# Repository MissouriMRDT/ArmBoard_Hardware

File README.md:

# RoboticArm-Hardware
Hardware design files for robotic arm

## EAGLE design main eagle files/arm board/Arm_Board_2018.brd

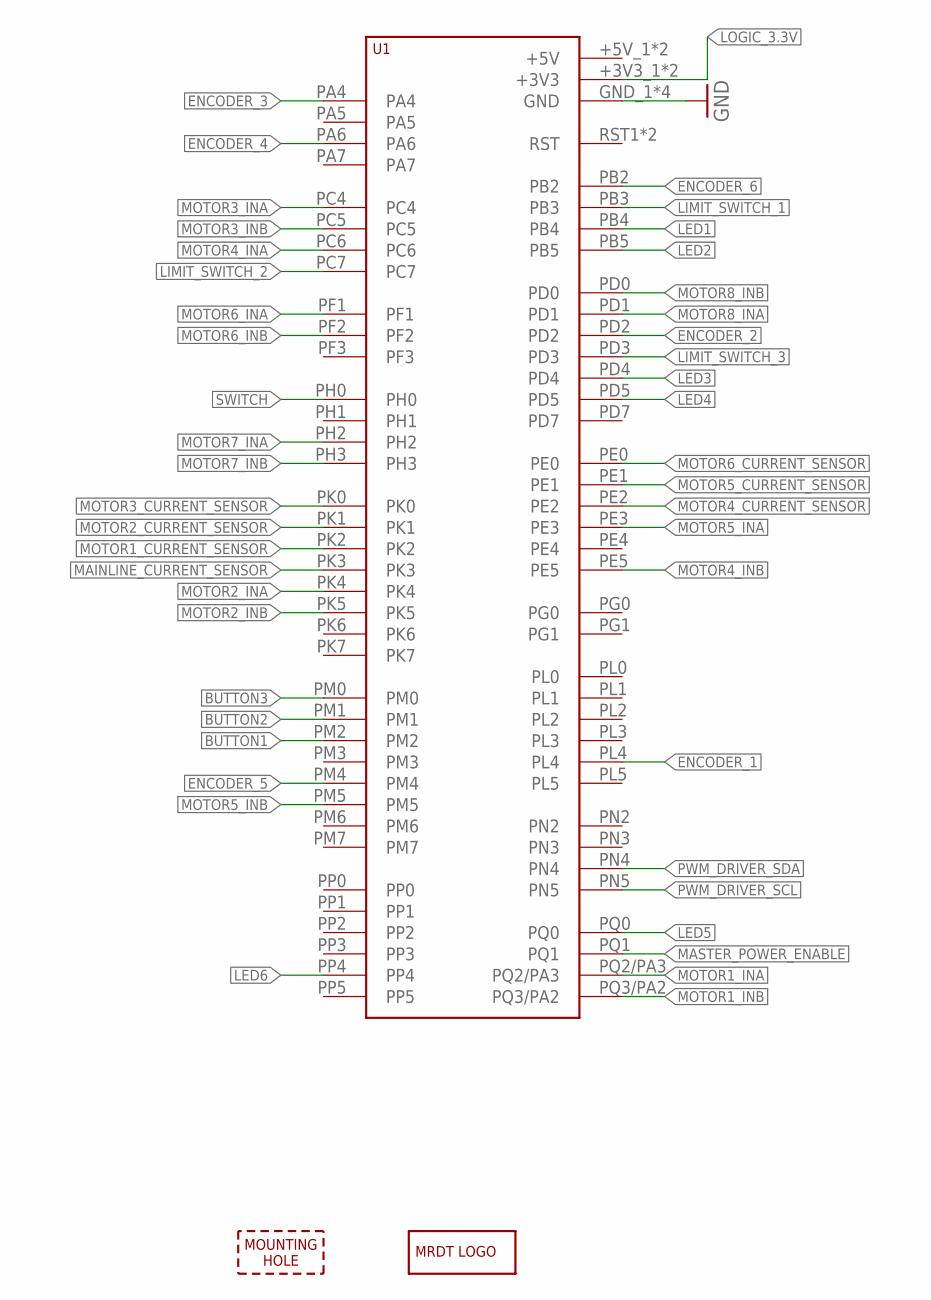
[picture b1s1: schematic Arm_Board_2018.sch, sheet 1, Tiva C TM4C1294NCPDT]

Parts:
H1: MOUNTING_HOLE#6; #6_SCREW
LOGO1: MRDT_LOGO
U1: TIVA-1294; TIVA-C-CONNECTED

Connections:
BUTTON1: U1.PM2; also elsewhere on the board
BUTTON2: U1.PM1; also elsewhere on the board
BUTTON3: U1.PM0; also elsewhere on the board
ENCODER_1: U1.PL4; also elsewhere on the board
ENCODER_2: U1.PD2; also elsewhere on the board
ENCODER_3: U1.PA4; also elsewhere on the board
ENCODER_4: U1.PA6; also elsewhere on the board
ENCODER_5: U1.PM4; also elsewhere on the board
ENCODER_6: U1.PB2; also elsewhere on the board
GND: U1.GND_1 (GND), U1.GND_2 (GND), U1.GND_3 (GND), U1.GND_4 (GND); also elsewhere on the board
LED1: U1.PB4; also elsewhere on the board
LED2: U1.PB5; also elsewhere on the board
LED3: U1.PD4; also elsewhere on the board
LED4: U1.PD5; also elsewhere on the board
LED5: U1.PQ0; also elsewhere on the board
LED6: U1.PP4; also elsewhere on the board
LIMIT_SWITCH_1: U1.PB3; also elsewhere on the board
LIMIT_SWITCH_2: U1.PC7; also elsewhere on the board
LIMIT_SWITCH_3: U1.PD3; also elsewhere on the board
LOGIC_3.3V: U1.+3V3_1 (+3V3), U1.+3V3_2 (+3V3); also elsewhere on the board
MAINLINE_CURRENT_SENSOR: U1.PK3; also elsewhere on the board
MASTER_POWER_ENABLE: U1.PQ1; also elsewhere on the board
MOTOR1_CURRENT_SENSOR: U1.PK2; also elsewhere on the board
MOTOR1_INA: U1.PQ2/PA3; also elsewhere on the board
MOTOR1_INB: U1.PQ3/PA2; also elsewhere on the board
MOTOR2_CURRENT_SENSOR: U1.PK1; also elsewhere on the board
MOTOR2_INA: U1.PK4; also elsewhere on the board
MOTOR2_INB: U1.PK5; also elsewhere on the board
MOTOR3_CURRENT_SENSOR: U1.PK0; also elsewhere on the board
MOTOR3_INA: U1.PC4; also elsewhere on the board
MOTOR3_INB: U1.PC5; also elsewhere on the board
MOTOR4_CURRENT_SENSOR: U1.PE2; also elsewhere on the board
MOTOR4_INA: U1.PC6; also elsewhere on the board
MOTOR4_INB: U1.PE5; also elsewhere on the board
MOTOR5_CURRENT_SENSOR: U1.PE1; also elsewhere on the board
MOTOR5_INA: U1.PE3; also elsewhere on the board
MOTOR5_INB: U1.PM5; also elsewhere on the board
MOTOR6_CURRENT_SENSOR: U1.PE0; also elsewhere on the board
MOTOR6_INA: U1.PF1; also elsewhere on the board
MOTOR6_INB: U1.PF2; also elsewhere on the board
MOTOR7_INA: U1.PH2; also elsewhere on the board
MOTOR7_INB: U1.PH3; also elsewhere on the board
MOTOR8_INA: U1.PD1; also elsewhere on the board
MOTOR8_INB: U1.PD0; also elsewhere on the board
PWM_DRIVER_SCL: U1.PN5; also elsewhere on the board
PWM_DRIVER_SDA: U1.PN4; also elsewhere on the board
SWITCH: U1.PH0; also elsewhere on the board

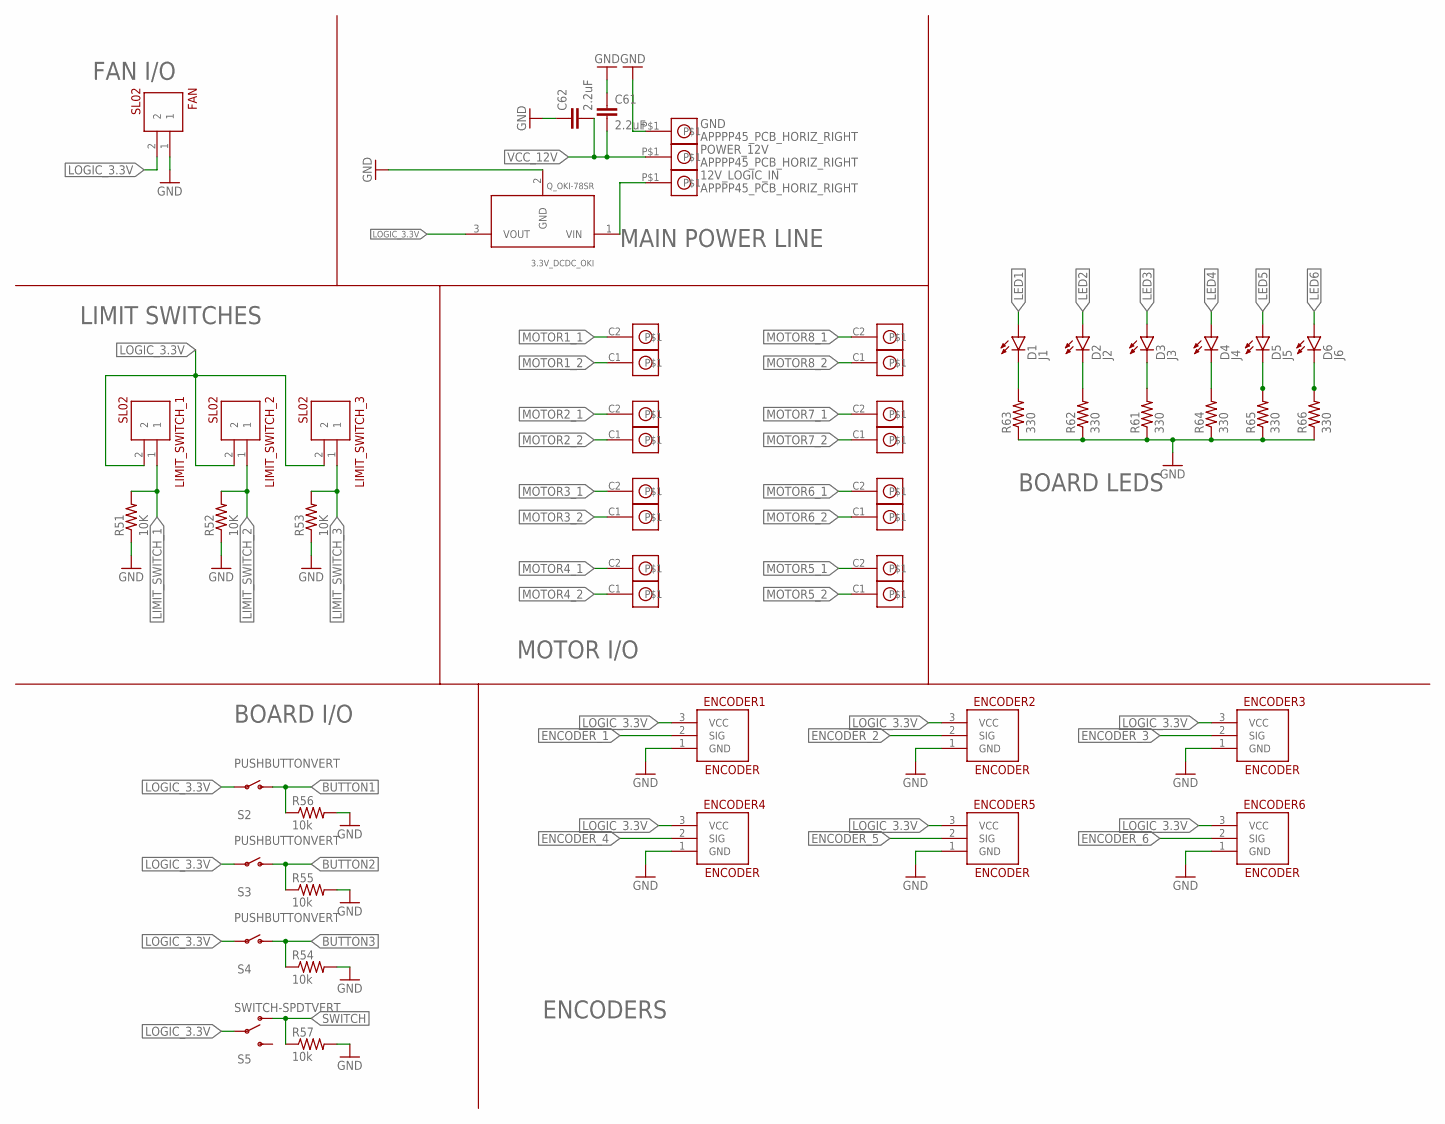
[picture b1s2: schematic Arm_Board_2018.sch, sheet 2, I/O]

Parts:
3.3V_DCDC_OKI: Q_OKI-78SR
12V_LOGIC_IN: APPPP45_PCB_HORIZ_RIGHT; APP45_PCB_HORIZ_RIGHT
C61, C62: 2.2uF; 1206
D1: J1; LED-0603
D2: J2; LED-0603
D3: J3; LED-0603
D4: J4; LED-0603
D5: J5; LED-0603
D6: J6; LED-0603
ENCODER1, ENCODER2, ENCODER3, ENCODER4, ENCODER5, ENCODER6: ENCODER; MOLEX-70543-0002
FAN: SL02; MOLEX-70543-0001
GND: APPPP45_PCB_HORIZ_RIGHT; APP45_PCB_HORIZ_RIGHT
LIMIT_SWITCH_1, LIMIT_SWITCH_2, LIMIT_SWITCH_3: SL02; MOLEX-70543-0001
MOTOR1, MOTOR2, MOTOR3, MOTOR4, MOTOR5, MOTOR6, MOTOR7, MOTOR8: APP_2POS_CONFIGGENERAL_CONFIG; APP45_HORIZ_CONFIG
POWER_12V: APPPP45_PCB_HORIZ_RIGHT; APP45_PCB_HORIZ_RIGHT
R51, R52, R53: 10K; 0402-RES
R54, R55, R56, R57: 10k; 0402-RES
R61, R62, R63, R64, R65, R66: 330; 0402-RES
S2, S3, S4: PUSHBUTTONVERT; APEM-MJTP1243
S5: SWITCH-SPDTVERT; C&K-SS12D07VG4NSGAPA

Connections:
BUTTON1: R56.1, S2.P$2 (S); also elsewhere on the board
BUTTON2: R55.1, S3.P$2 (S); also elsewhere on the board
BUTTON3: R54.1, S4.P$2 (S); also elsewhere on the board
ENCODER_1: ENCODER1.2 (SIG); also elsewhere on the board
ENCODER_2: ENCODER2.2 (SIG); also elsewhere on the board
ENCODER_3: ENCODER3.2 (SIG); also elsewhere on the board
ENCODER_4: ENCODER4.2 (SIG); also elsewhere on the board
ENCODER_5: ENCODER5.2 (SIG); also elsewhere on the board
ENCODER_6: ENCODER6.2 (SIG); also elsewhere on the board
GND: 3.3V_DCDC_OKI.2 (GND), C61.1, C62.1, ENCODER1.1 (GND), ENCODER2.1 (GND), ENCODER3.1 (GND), ENCODER4.1 (GND), ENCODER5.1 (GND), ENCODER6.1 (GND), FAN.1, GND.P$1, R51.1, R52.1, R53.1, R54.2, R55.2, R56.2, R57.2, R61.1, R62.1, R63.1, R64.1, R65.1, R66.1; also elsewhere on the board
LED1: D1.A; also elsewhere on the board
LED2: D2.A; also elsewhere on the board
LED3: D3.A; also elsewhere on the board
LED4: D4.A; also elsewhere on the board
LED5: D5.A; also elsewhere on the board
LED6: D6.A; also elsewhere on the board
LIMIT_SWITCH_1: LIMIT_SWITCH_1.1, R51.2; also elsewhere on the board
LIMIT_SWITCH_2: LIMIT_SWITCH_2.1, R52.2; also elsewhere on the board
LIMIT_SWITCH_3: LIMIT_SWITCH_3.1, R53.2; also elsewhere on the board
LOGIC_3.3V: 3.3V_DCDC_OKI.3 (VOUT), ENCODER1.3 (VCC), ENCODER2.3 (VCC), ENCODER3.3 (VCC), ENCODER4.3 (VCC), ENCODER5.3 (VCC), ENCODER6.3 (VCC), FAN.2, LIMIT_SWITCH_1.2, LIMIT_SWITCH_2.2, LIMIT_SWITCH_3.2, S2.P$1, S3.P$1, S4.P$1, S5.P$2; also elsewhere on the board
MOTOR1_1: MOTOR1.C2; also elsewhere on the board
MOTOR1_2: MOTOR1.C1; also elsewhere on the board
MOTOR2_1: MOTOR2.C2; also elsewhere on the board
MOTOR2_2: MOTOR2.C1; also elsewhere on the board
MOTOR3_1: MOTOR3.C2; also elsewhere on the board
MOTOR3_2: MOTOR3.C1; also elsewhere on the board
MOTOR4_1: MOTOR4.C2; also elsewhere on the board
MOTOR4_2: MOTOR4.C1; also elsewhere on the board
MOTOR5_1: MOTOR5.C2; also elsewhere on the board
MOTOR5_2: MOTOR5.C1; also elsewhere on the board
MOTOR6_1: MOTOR6.C2; also elsewhere on the board
MOTOR6_2: MOTOR6.C1; also elsewhere on the board
MOTOR7_1: MOTOR7.C2; also elsewhere on the board
MOTOR7_2: MOTOR7.C1; also elsewhere on the board
MOTOR8_1: MOTOR8.C2; also elsewhere on the board
MOTOR8_2: MOTOR8.C1; also elsewhere on the board
unnamed: 3.3V_DCDC_OKI.1 (VIN), 12V_LOGIC_IN.P$1
unnamed: D1.C, R63.2
unnamed: D2.C, R62.2
unnamed: D6.C, R66.2
unnamed: D3.C, R61.2
unnamed: D4.C, R64.2
unnamed: D5.C, R65.2
SWITCH: R57.1, S5.P$3 (O); also elsewhere on the board
VCC_12V: C61.2, C62.2, POWER_12V.P$1; also elsewhere on the board

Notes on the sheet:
FAN I/O
MOTOR I/O
MAIN POWER LINE
LIMIT SWITCHES
ENCODERS
BOARD I/O
BOARD LEDS

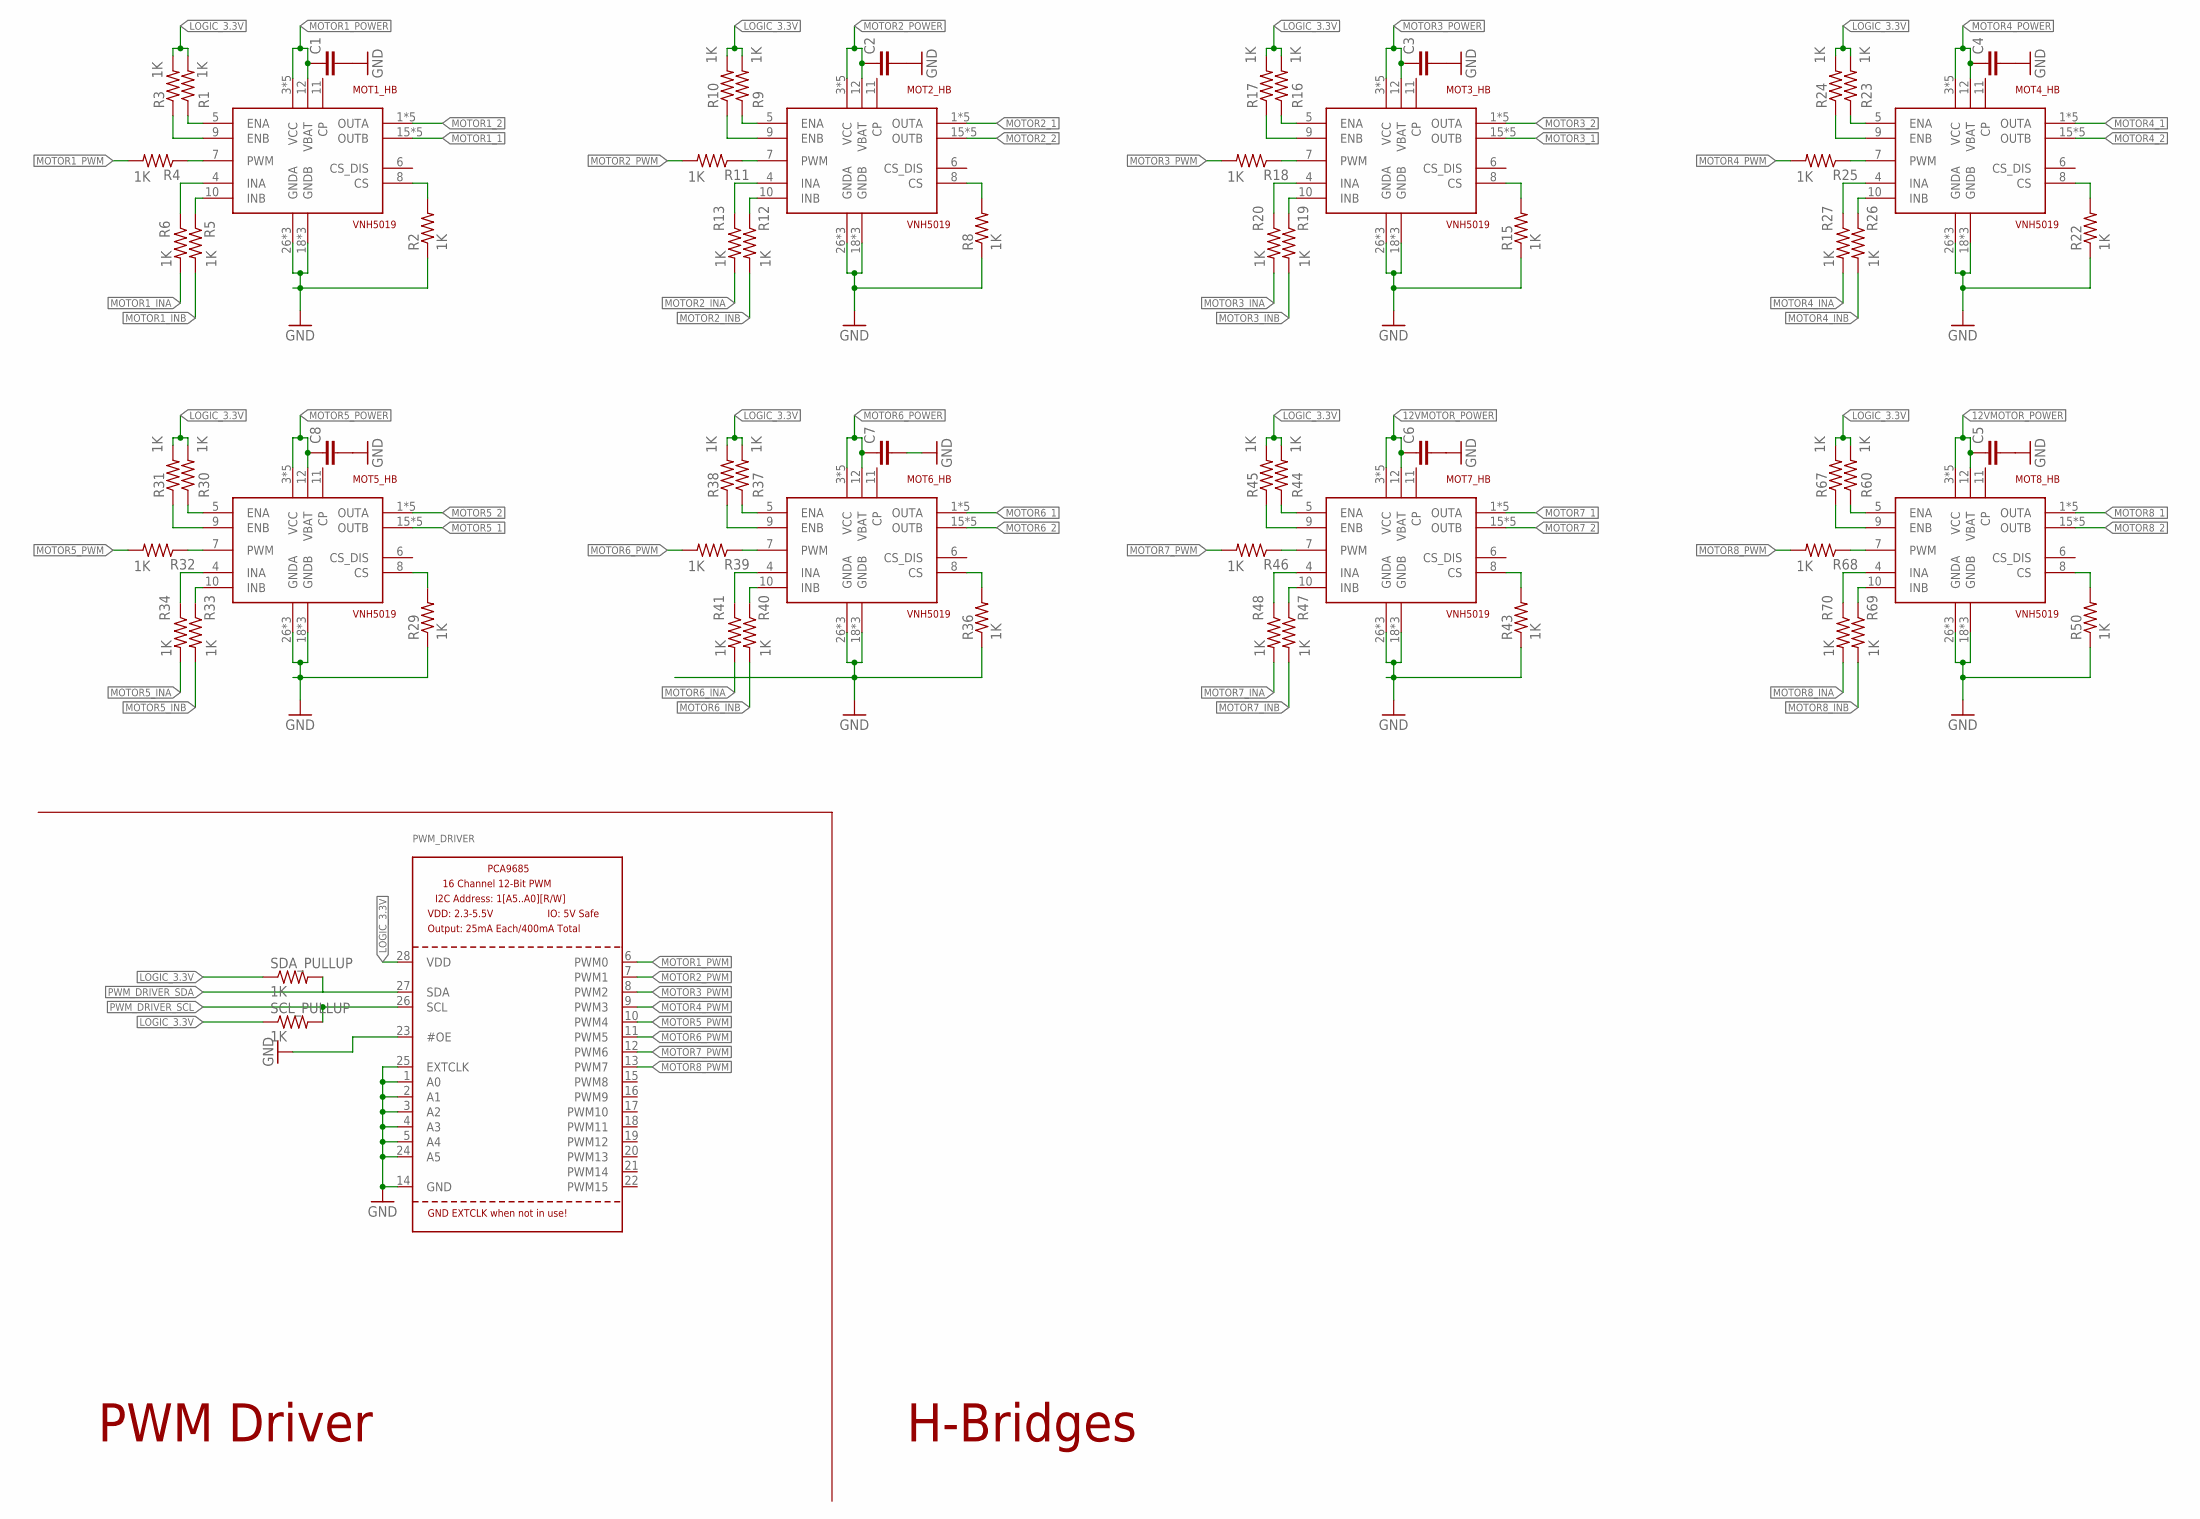
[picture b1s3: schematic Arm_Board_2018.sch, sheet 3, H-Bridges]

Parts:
C1, C2, C3, C4, C5, C6, C7, C8: CAP1210; 1210
MOT1_HB, MOT2_HB, MOT3_HB, MOT4_HB, MOT5_HB, MOT6_HB, MOT7_HB, MOT8_HB: VNH5019; MULTIPOWERSO-30
PWM_DRIVER: PCA9685; TSSOP28
R1, R2, R3, R4, R5, R6, R8, R9, R10, R11, R12, R13, R15, R16, R17, R18, R19, R20, R22, R23, R24, R25, R26, R27, R29, R30, R31, R32, R33, R34, R36, R37, R38, R39, R40, R41, R43, R44, R45, R46, R47, R48, R50, R60, R67, R68, R69, R70: 1K; 0603-RES
SCL_PULLUP: 1K; 0402-RES
SDA_PULLUP: 1K; 0402-RES

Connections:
12VMOTOR_POWER: C5.1, C6.1, MOT7_HB.3 (VCC), MOT7_HB.12 (VBAT), MOT7_HB.13 (VCC), MOT7_HB.23 (VCC), MOT7_HB.VCC, MOT7_HB.VCC@1 (VCC), MOT8_HB.3 (VCC), MOT8_HB.12 (VBAT), MOT8_HB.13 (VCC), MOT8_HB.23 (VCC), MOT8_HB.VCC, MOT8_HB.VCC@1 (VCC); also elsewhere on the board
GND: C1.2, C2.2, C3.2, C4.2, C5.2, C6.2, C7.2, C8.2, MOT1_HB.18 (GNDB), MOT1_HB.19 (GNDB), MOT1_HB.20 (GNDB), MOT1_HB.26 (GNDA), MOT1_HB.27 (GNDA), MOT1_HB.28 (GNDA), MOT2_HB.18 (GNDB), MOT2_HB.19 (GNDB), MOT2_HB.20 (GNDB), MOT2_HB.26 (GNDA), MOT2_HB.27 (GNDA), MOT2_HB.28 (GNDA), MOT3_HB.18 (GNDB), MOT3_HB.19 (GNDB), MOT3_HB.20 (GNDB), MOT3_HB.26 (GNDA), MOT3_HB.27 (GNDA), MOT3_HB.28 (GNDA), MOT4_HB.18 (GNDB), MOT4_HB.19 (GNDB), MOT4_HB.20 (GNDB), MOT4_HB.26 (GNDA), MOT4_HB.27 (GNDA), MOT4_HB.28 (GNDA), MOT5_HB.18 (GNDB), MOT5_HB.19 (GNDB), MOT5_HB.20 (GNDB), MOT5_HB.26 (GNDA), MOT5_HB.27 (GNDA), MOT5_HB.28 (GNDA), MOT6_HB.18 (GNDB), MOT6_HB.19 (GNDB), MOT6_HB.20 (GNDB), MOT6_HB.26 (GNDA), MOT6_HB.27 (GNDA), MOT6_HB.28 (GNDA), MOT7_HB.18 (GNDB), MOT7_HB.19 (GNDB), MOT7_HB.20 (GNDB), MOT7_HB.26 (GNDA), MOT7_HB.27 (GNDA), MOT7_HB.28 (GNDA), MOT8_HB.18 (GNDB), MOT8_HB.19 (GNDB), MOT8_HB.20 (GNDB), MOT8_HB.26 (GNDA), MOT8_HB.27 (GNDA), MOT8_HB.28 (GNDA), PWM_DRIVER.1 (A0), PWM_DRIVER.2 (A1), PWM_DRIVER.3 (A2), PWM_DRIVER.4 (A3), PWM_DRIVER.5 (A4), PWM_DRIVER.14 (GND), PWM_DRIVER.23 (#OE), PWM_DRIVER.24 (A5), PWM_DRIVER.25 (EXTCLK), R2.1, R8.1, R15.1, R22.1, R29.1, R36.1, R43.1, R50.1; also elsewhere on the board
LOGIC_3.3V: PWM_DRIVER.28 (VDD), R1.2, R3.2, R9.2, R10.2, R16.2, R17.2, R23.2, R24.2, R30.2, R31.2, R37.2, R38.2, R44.2, R45.2, R60.2, R67.2, SCL_PULLUP.1, SDA_PULLUP.1; also elsewhere on the board
MOTOR1_1: MOT1_HB.15 (OUTB), MOT1_HB.16 (OUTB), MOT1_HB.21 (OUTB), MOT1_HB.OUTB, MOT1_HB.OUTB@1 (OUTB); also elsewhere on the board
MOTOR1_2: MOT1_HB.1 (OUTA), MOT1_HB.25 (OUTA), MOT1_HB.30 (OUTA), MOT1_HB.OUTA, MOT1_HB.OUTA@1 (OUTA); also elsewhere on the board
MOTOR1_INA: R6.2; also elsewhere on the board
MOTOR1_INB: R5.2; also elsewhere on the board
MOTOR1_POWER: C1.1, MOT1_HB.3 (VCC), MOT1_HB.12 (VBAT), MOT1_HB.13 (VCC), MOT1_HB.23 (VCC), MOT1_HB.VCC, MOT1_HB.VCC@1 (VCC); also elsewhere on the board
MOTOR1_PWM: PWM_DRIVER.6 (PWM0), R4.2
MOTOR2_1: MOT2_HB.1 (OUTA), MOT2_HB.25 (OUTA), MOT2_HB.30 (OUTA), MOT2_HB.OUTA, MOT2_HB.OUTA@1 (OUTA); also elsewhere on the board
MOTOR2_2: MOT2_HB.15 (OUTB), MOT2_HB.16 (OUTB), MOT2_HB.21 (OUTB), MOT2_HB.OUTB, MOT2_HB.OUTB@1 (OUTB); also elsewhere on the board
MOTOR2_INA: R13.2; also elsewhere on the board
MOTOR2_INB: R12.2; also elsewhere on the board
MOTOR2_POWER: C2.1, MOT2_HB.3 (VCC), MOT2_HB.12 (VBAT), MOT2_HB.13 (VCC), MOT2_HB.23 (VCC), MOT2_HB.VCC, MOT2_HB.VCC@1 (VCC); also elsewhere on the board
MOTOR2_PWM: PWM_DRIVER.7 (PWM1), R11.2
MOTOR3_1: MOT3_HB.15 (OUTB), MOT3_HB.16 (OUTB), MOT3_HB.21 (OUTB), MOT3_HB.OUTB, MOT3_HB.OUTB@1 (OUTB); also elsewhere on the board
MOTOR3_2: MOT3_HB.1 (OUTA), MOT3_HB.25 (OUTA), MOT3_HB.30 (OUTA), MOT3_HB.OUTA, MOT3_HB.OUTA@1 (OUTA); also elsewhere on the board
MOTOR3_INA: R20.2; also elsewhere on the board
MOTOR3_INB: R19.2; also elsewhere on the board
MOTOR3_POWER: C3.1, MOT3_HB.3 (VCC), MOT3_HB.12 (VBAT), MOT3_HB.13 (VCC), MOT3_HB.23 (VCC), MOT3_HB.VCC, MOT3_HB.VCC@1 (VCC); also elsewhere on the board
MOTOR3_PWM: PWM_DRIVER.8 (PWM2), R18.2
MOTOR4_1: MOT4_HB.1 (OUTA), MOT4_HB.25 (OUTA), MOT4_HB.30 (OUTA), MOT4_HB.OUTA, MOT4_HB.OUTA@1 (OUTA); also elsewhere on the board
MOTOR4_2: MOT4_HB.15 (OUTB), MOT4_HB.16 (OUTB), MOT4_HB.21 (OUTB), MOT4_HB.OUTB, MOT4_HB.OUTB@1 (OUTB); also elsewhere on the board
MOTOR4_INA: R27.2; also elsewhere on the board
MOTOR4_INB: R26.2; also elsewhere on the board
MOTOR4_POWER: C4.1, MOT4_HB.3 (VCC), MOT4_HB.12 (VBAT), MOT4_HB.13 (VCC), MOT4_HB.23 (VCC), MOT4_HB.VCC, MOT4_HB.VCC@1 (VCC); also elsewhere on the board
MOTOR4_PWM: PWM_DRIVER.9 (PWM3), R25.2
MOTOR5_1: MOT5_HB.15 (OUTB), MOT5_HB.16 (OUTB), MOT5_HB.21 (OUTB), MOT5_HB.OUTB, MOT5_HB.OUTB@1 (OUTB); also elsewhere on the board
MOTOR5_2: MOT5_HB.1 (OUTA), MOT5_HB.25 (OUTA), MOT5_HB.30 (OUTA), MOT5_HB.OUTA, MOT5_HB.OUTA@1 (OUTA); also elsewhere on the board
MOTOR5_INA: R34.2; also elsewhere on the board
MOTOR5_INB: R33.2; also elsewhere on the board
MOTOR5_POWER: C8.1, MOT5_HB.3 (VCC), MOT5_HB.12 (VBAT), MOT5_HB.13 (VCC), MOT5_HB.23 (VCC), MOT5_HB.VCC, MOT5_HB.VCC@1 (VCC); also elsewhere on the board
MOTOR5_PWM: PWM_DRIVER.10 (PWM4), R32.2
MOTOR6_1: MOT6_HB.1 (OUTA), MOT6_HB.25 (OUTA), MOT6_HB.30 (OUTA), MOT6_HB.OUTA, MOT6_HB.OUTA@1 (OUTA); also elsewhere on the board
MOTOR6_2: MOT6_HB.15 (OUTB), MOT6_HB.16 (OUTB), MOT6_HB.21 (OUTB), MOT6_HB.OUTB, MOT6_HB.OUTB@1 (OUTB); also elsewhere on the board
MOTOR6_INA: R41.2; also elsewhere on the board
MOTOR6_INB: R40.2; also elsewhere on the board
MOTOR6_POWER: C7.1, MOT6_HB.3 (VCC), MOT6_HB.12 (VBAT), MOT6_HB.13 (VCC), MOT6_HB.23 (VCC), MOT6_HB.VCC, MOT6_HB.VCC@1 (VCC); also elsewhere on the board
MOTOR6_PWM: PWM_DRIVER.11 (PWM5), R39.2
MOTOR7_1: MOT7_HB.1 (OUTA), MOT7_HB.25 (OUTA), MOT7_HB.30 (OUTA), MOT7_HB.OUTA, MOT7_HB.OUTA@1 (OUTA); also elsewhere on the board
MOTOR7_2: MOT7_HB.15 (OUTB), MOT7_HB.16 (OUTB), MOT7_HB.21 (OUTB), MOT7_HB.OUTB, MOT7_HB.OUTB@1 (OUTB); also elsewhere on the board
MOTOR7_INA: R48.2; also elsewhere on the board
MOTOR7_INB: R47.2; also elsewhere on the board
MOTOR7_PWM: PWM_DRIVER.12 (PWM6), R46.2
MOTOR8_1: MOT8_HB.1 (OUTA), MOT8_HB.25 (OUTA), MOT8_HB.30 (OUTA), MOT8_HB.OUTA, MOT8_HB.OUTA@1 (OUTA); also elsewhere on the board
MOTOR8_2: MOT8_HB.15 (OUTB), MOT8_HB.16 (OUTB), MOT8_HB.21 (OUTB), MOT8_HB.OUTB, MOT8_HB.OUTB@1 (OUTB); also elsewhere on the board
MOTOR8_INA: R70.2; also elsewhere on the board
MOTOR8_INB: R69.2; also elsewhere on the board
MOTOR8_PWM: PWM_DRIVER.13 (PWM7), R68.2
unnamed: MOT2_HB.8 (CS), R8.2
unnamed: MOT1_HB.8 (CS), R2.2
unnamed: MOT1_HB.5 (ENA), R1.1
unnamed: MOT1_HB.9 (ENB), R3.1
unnamed: MOT1_HB.7 (PWM), R4.1
unnamed: MOT1_HB.10 (INB), R5.1
unnamed: MOT1_HB.4 (INA), R6.1
unnamed: MOT2_HB.5 (ENA), R9.1
unnamed: MOT2_HB.9 (ENB), R10.1
unnamed: MOT2_HB.7 (PWM), R11.1
unnamed: MOT2_HB.10 (INB), R12.1
unnamed: MOT2_HB.4 (INA), R13.1
unnamed: MOT3_HB.8 (CS), R15.2
unnamed: MOT3_HB.5 (ENA), R16.1
unnamed: MOT3_HB.9 (ENB), R17.1
unnamed: MOT3_HB.7 (PWM), R18.1
unnamed: MOT3_HB.10 (INB), R19.1
unnamed: MOT3_HB.4 (INA), R20.1
unnamed: MOT4_HB.8 (CS), R22.2
unnamed: MOT4_HB.5 (ENA), R23.1
unnamed: MOT4_HB.9 (ENB), R24.1
unnamed: MOT4_HB.7 (PWM), R25.1
unnamed: MOT4_HB.10 (INB), R26.1
unnamed: MOT4_HB.4 (INA), R27.1
unnamed: MOT5_HB.8 (CS), R29.2
unnamed: MOT5_HB.5 (ENA), R30.1
unnamed: MOT5_HB.9 (ENB), R31.1
unnamed: MOT5_HB.7 (PWM), R32.1
unnamed: MOT5_HB.10 (INB), R33.1
unnamed: MOT5_HB.4 (INA), R34.1
unnamed: MOT6_HB.8 (CS), R36.2
unnamed: MOT6_HB.5 (ENA), R37.1
unnamed: MOT6_HB.9 (ENB), R38.1
unnamed: MOT6_HB.7 (PWM), R39.1
unnamed: MOT6_HB.10 (INB), R40.1
unnamed: MOT6_HB.4 (INA), R41.1
unnamed: MOT7_HB.8 (CS), R43.2
unnamed: MOT7_HB.5 (ENA), R44.1
unnamed: MOT7_HB.9 (ENB), R45.1
unnamed: MOT7_HB.7 (PWM), R46.1
unnamed: MOT7_HB.10 (INB), R47.1
unnamed: MOT7_HB.4 (INA), R48.1
unnamed: MOT8_HB.8 (CS), R50.2
unnamed: MOT8_HB.5 (ENA), R60.1
unnamed: MOT8_HB.9 (ENB), R67.1
unnamed: MOT8_HB.7 (PWM), R68.1
unnamed: MOT8_HB.10 (INB), R69.1
unnamed: MOT8_HB.4 (INA), R70.1
PWM_DRIVER_SCL: PWM_DRIVER.26 (SCL), SCL_PULLUP.2; also elsewhere on the board
PWM_DRIVER_SDA: PWM_DRIVER.27 (SDA), SDA_PULLUP.2; also elsewhere on the board

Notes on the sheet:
PWM Driver
H-Bridges

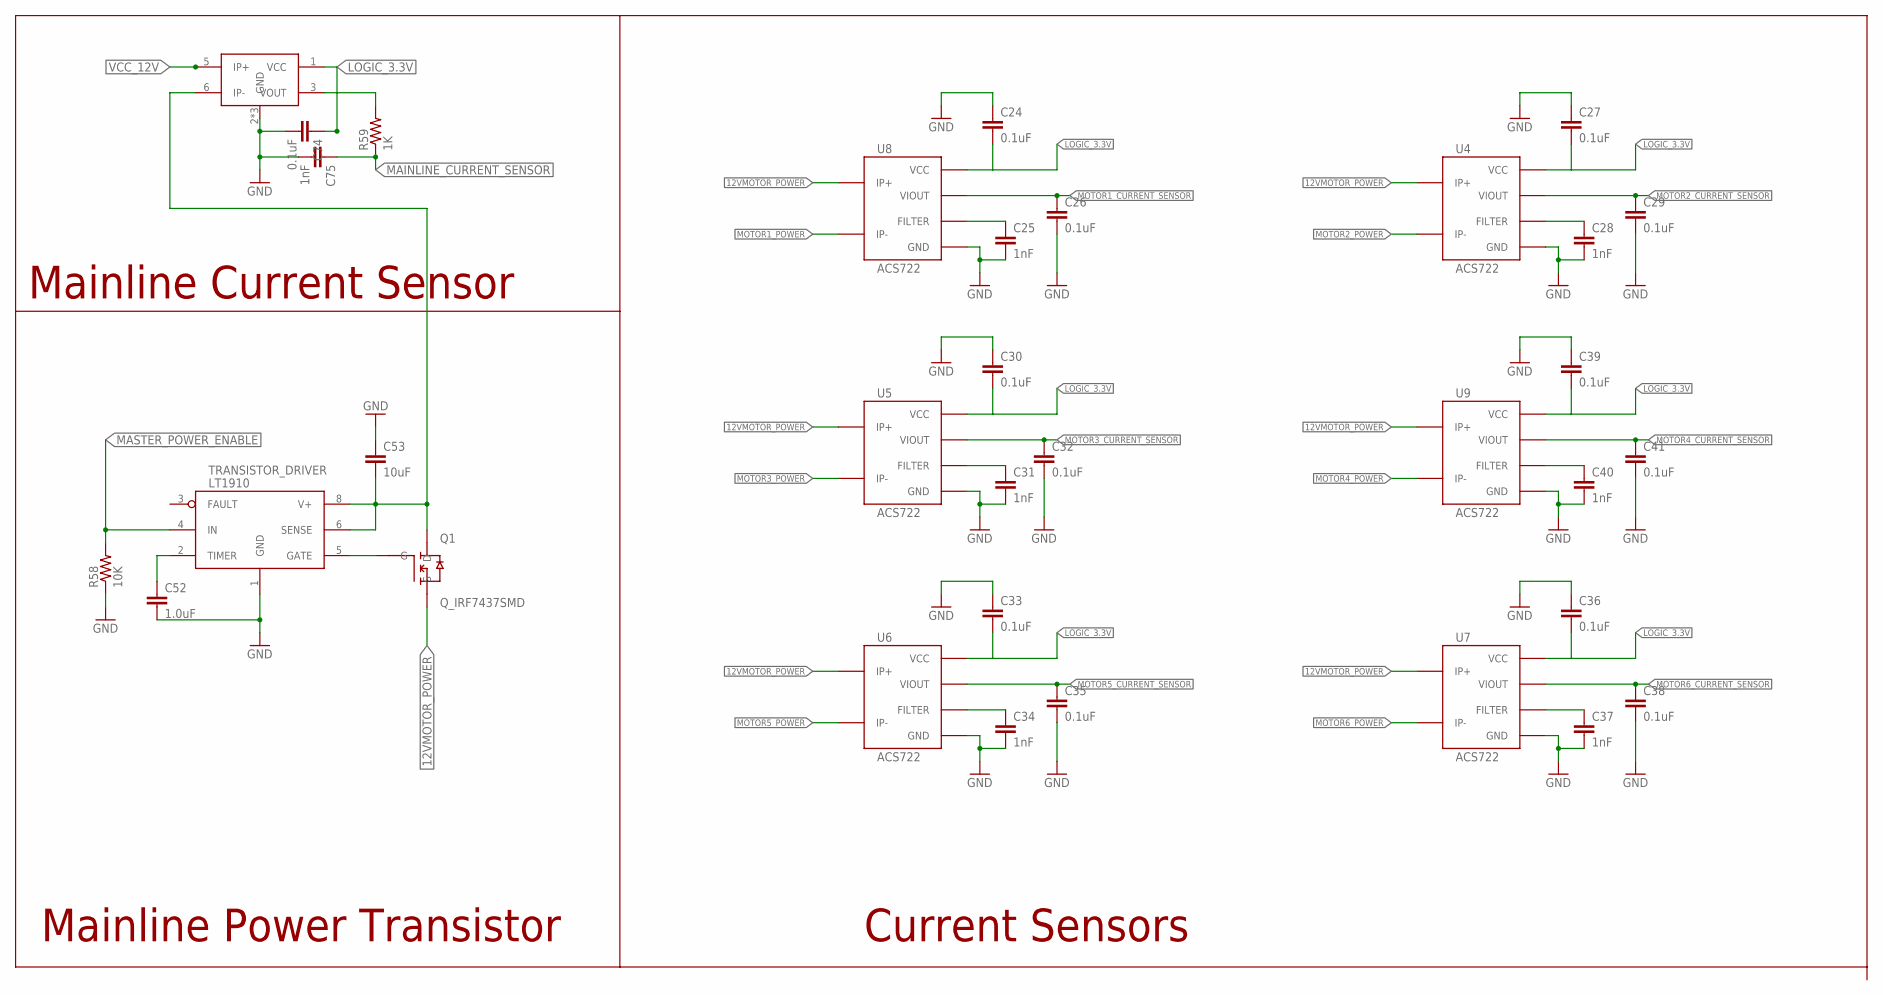
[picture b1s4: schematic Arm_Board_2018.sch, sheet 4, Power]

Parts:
C24, C26, C27, C29, C30, C32, C33, C35, C36, C38, C39, C41, C74: 0.1uF; 0603-CAP
C25, C28, C31, C34, C37, C40, C75: 1nF; 0603-CAP
C52: 1.0uF; 0603-CAP
C53: 10uF; 0603-CAP
MAINLINE_CURRENT: ACS781; 7-POWER_SMD_MODULE
Q1: Q_IRF7437SMD; D2PACK
R58: 10K; 0402-RES
R59: 1K; 0402-RES
TRANSISTOR_DRIVER: LT1910; SO8
U4, U5, U6, U7, U8, U9: ACS722; SOIC8

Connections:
12VMOTOR_POWER: Q1.2 (S), U4.1 (IP+), U4.2 (IP+), U5.1 (IP+), U5.2 (IP+), U6.1 (IP+), U6.2 (IP+), U7.1 (IP+), U7.2 (IP+), U8.1 (IP+), U8.2 (IP+), U9.1 (IP+), U9.2 (IP+); also elsewhere on the board
GND: C24.1, C25.2, C26.2, C27.1, C28.2, C29.2, C30.1, C31.2, C32.2, C33.1, C34.2, C35.2, C36.1, C37.2, C38.2, C39.1, C40.2, C41.2, C52.2, C53.1, C74.2, C75.2, MAINLINE_CURRENT.2 (GND), MAINLINE_CURRENT.4 (GND), MAINLINE_CURRENT.7 (GND), R58.1, TRANSISTOR_DRIVER.1 (GND), U4.5 (GND), U5.5 (GND), U6.5 (GND), U7.5 (GND), U8.5 (GND), U9.5 (GND); also elsewhere on the board
LOGIC_3.3V: C24.2, C27.2, C30.2, C33.2, C36.2, C39.2, C74.1, MAINLINE_CURRENT.1 (VCC), U4.8 (VCC), U5.8 (VCC), U6.8 (VCC), U7.8 (VCC), U8.8 (VCC), U9.8 (VCC); also elsewhere on the board
MAINLINE_CURRENT_SENSOR: C75.1, R59.1; also elsewhere on the board
MASTER_POWER_ENABLE: R58.2, TRANSISTOR_DRIVER.4 (IN); also elsewhere on the board
MOTOR1_CURRENT_SENSOR: C26.1, U8.7 (VIOUT); also elsewhere on the board
MOTOR1_POWER: U8.3 (IP-), U8.4 (IP-); also elsewhere on the board
MOTOR2_CURRENT_SENSOR: C29.1, U4.7 (VIOUT); also elsewhere on the board
MOTOR2_POWER: U4.3 (IP-), U4.4 (IP-); also elsewhere on the board
MOTOR3_CURRENT_SENSOR: C32.1, U5.7 (VIOUT); also elsewhere on the board
MOTOR3_POWER: U5.3 (IP-), U5.4 (IP-); also elsewhere on the board
MOTOR4_CURRENT_SENSOR: C41.1, U9.7 (VIOUT); also elsewhere on the board
MOTOR4_POWER: U9.3 (IP-), U9.4 (IP-); also elsewhere on the board
MOTOR5_CURRENT_SENSOR: C35.1, U6.7 (VIOUT); also elsewhere on the board
MOTOR5_POWER: U6.3 (IP-), U6.4 (IP-); also elsewhere on the board
MOTOR6_CURRENT_SENSOR: C38.1, U7.7 (VIOUT); also elsewhere on the board
MOTOR6_POWER: U7.3 (IP-), U7.4 (IP-); also elsewhere on the board
unnamed: C28.1, U4.6 (FILTER)
unnamed: C52.1, TRANSISTOR_DRIVER.2 (TIMER)
unnamed: C25.1, U8.6 (FILTER)
unnamed: C31.1, U5.6 (FILTER)
unnamed: C34.1, U6.6 (FILTER)
unnamed: C37.1, U7.6 (FILTER)
unnamed: C40.1, U9.6 (FILTER)
unnamed: Q1.1 (G), TRANSISTOR_DRIVER.5 (GATE)
unnamed: C53.2, MAINLINE_CURRENT.6 (IP-), Q1.TAB (D), TRANSISTOR_DRIVER.6 (SENSE), TRANSISTOR_DRIVER.8 (V+)
unnamed: MAINLINE_CURRENT.3 (VOUT), R59.2
VCC_12V: MAINLINE_CURRENT.5 (IP+); also elsewhere on the board

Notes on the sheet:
Current Sensors
Mainline Current Sensor
Mainline Power Transistor

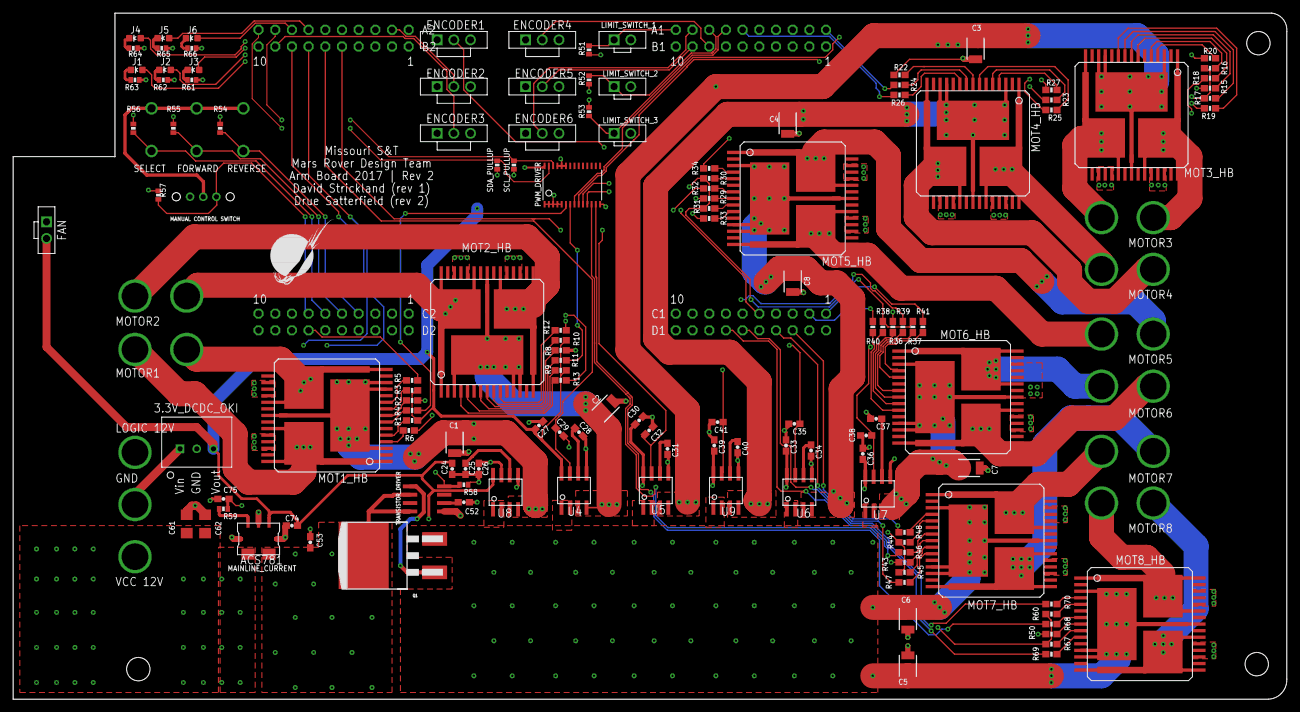
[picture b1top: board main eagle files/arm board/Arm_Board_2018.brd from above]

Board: 4 copper layers, 193.8 x 104.4 mm, 152 parts (0 on the bottom side), 144 nets.

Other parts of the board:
U$5, U$30: MOUNTING_HOLE#6; #6_SCREW

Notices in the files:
parts and their libraries:
SparkFun-Passives: Licensing: Creative Commons ShareAlike 4.0 International - https://creativecommons.org/licenses/by-sa/4.0
SparkFun-Capacitors: Licensing: CC v3.0 Share-Alike You are welcome to use this library for commercial purposes.
